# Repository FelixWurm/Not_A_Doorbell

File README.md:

# Not_A_Doorbell
This is a project aimed to build a custom "HotKey" board or mini Keyboard, using the raspberry pi pico (rp2040), an old recyceld controller (can by replaced with a standart alps encoder) and a qmc firmware. The used switches are cherry MX and compatiblt options.  It also uses RGB leds for some sweet lighing effects

The Name of the Project was selected because an early render of the device looked somewhat like a Doorbell, mainly because i only renderd the Encoder but not the buttons. 

# The Goal of the Project

I had purched a old "Video schnittpult" second hand (Televela T701), to use the housing and some of the parts for a different Project. However, the very nice encoder (also nown as jog/shutter wheel) was not realy needte. I howeve always whanted something to controll playing music with, so the idear was born to build my owen mini Keyboard.

#some tips:
in oder tu use the full potential of the endoder when usung linux set I recomend chnaging the amount the Volume chnages pear rotation to one ore two. To du this (if you are on ubuntu ):
- ``` gsettings get org.gnome.settings-daemon.plugins.media-keys volume-step ```
 - to get the currently set value
- ``` gsettings set org.gnome.settings-daemon.plugins.media-keys volume-step 1```
 - to set it to one

# PCB and Scematic

The pcb is designt in KiCad and manufacured by JLC PCB in china. THE CUURENT VERSION OF THIS PCB HAS SOME ISSUES! the issues are:
- Missing resistors for clampung voltage to 3.3 on the imput of the pico
- wrong hole placment of the lower mountung hole from the encoder
- general mounting hole misplacment

# Enclusure
- the optiginal idear for the hosing was to use wood, however in the current state that could by difficult to do with the mashines i have acsess to. 
- a STL housing that could by 3d Printet as well as a keyplate is in development
- there is a possibility for a CNC carved housung 

# ToDo 
- Fix the PCB
- Create the software
- Upload Pictures 
- Create the STL Files for the case

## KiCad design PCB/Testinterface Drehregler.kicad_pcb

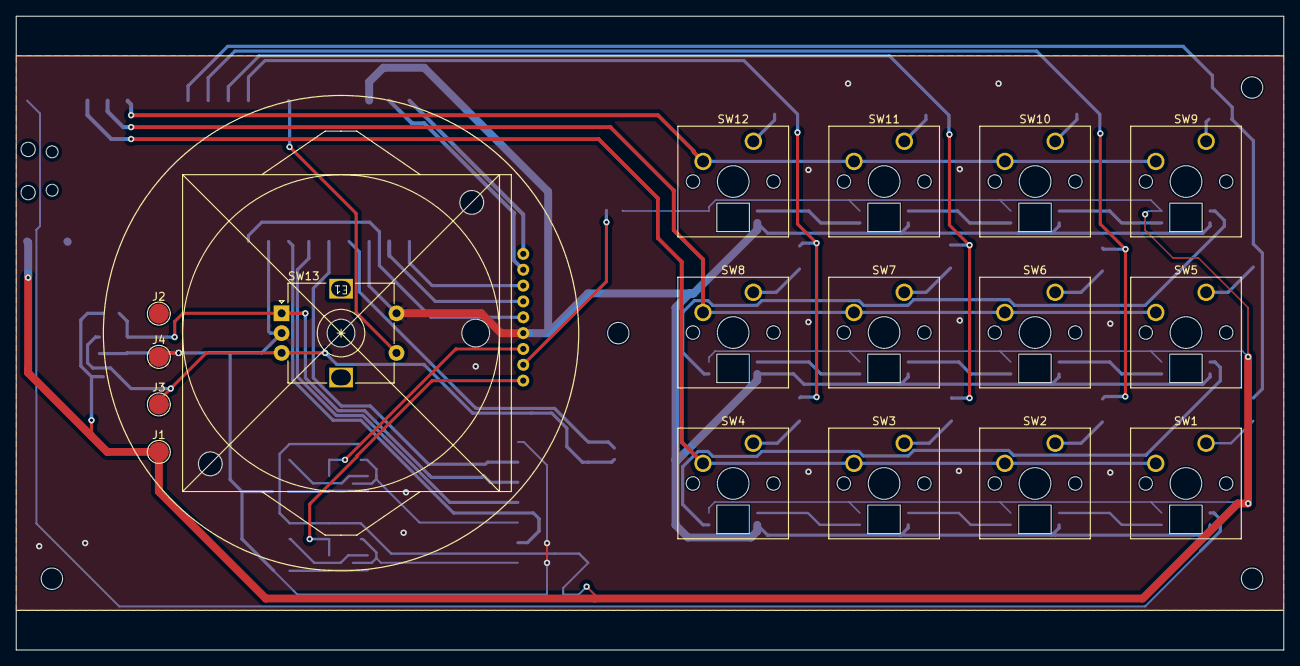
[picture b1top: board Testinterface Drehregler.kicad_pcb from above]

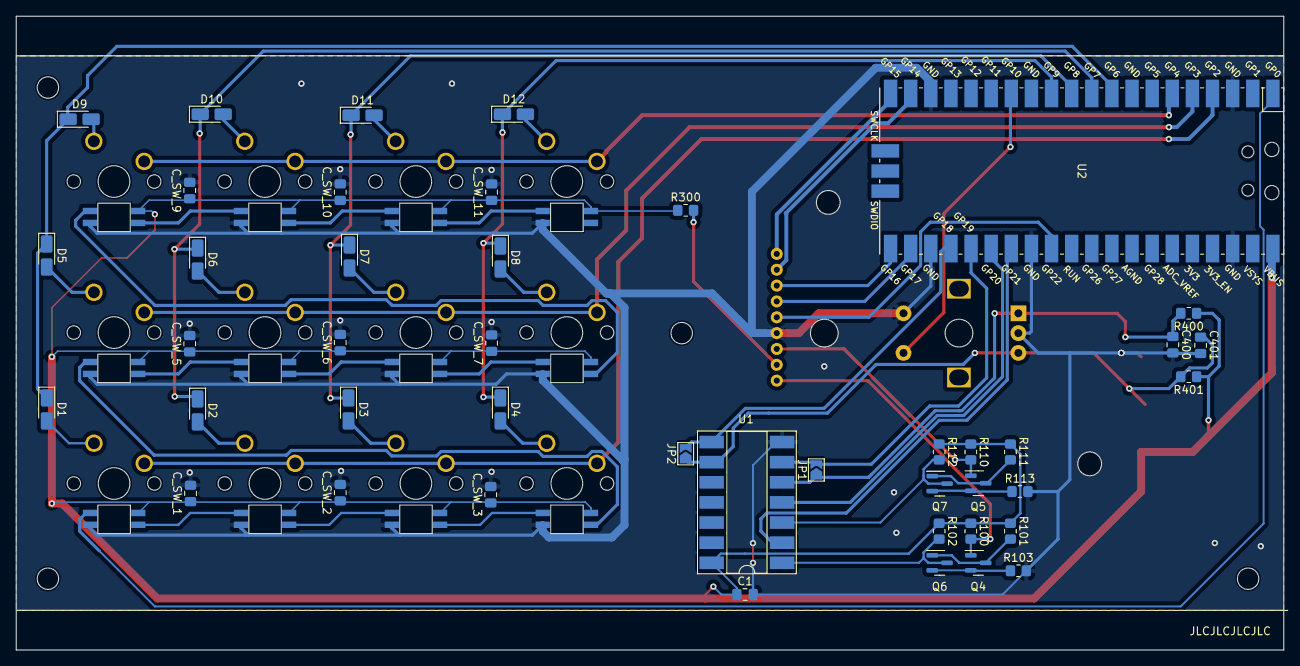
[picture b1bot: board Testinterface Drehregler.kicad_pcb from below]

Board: 2 copper layers, 160.0 x 80.0 mm, 65 parts (43 on the bottom side), 54 nets.

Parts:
C1: 100n; C_0805_2012Metric_Pad1.18x1.45mm_HandSolder
C400, C401: C; C_0805_2012Metric_Pad1.18x1.45mm_HandSolder
C_SW_1, C_SW_2, C_SW_3, C_SW_5, C_SW_6, C_SW_7, C_SW_9, C_SW_10, C_SW_11: 100nF; C_0805_2012Metric_Pad1.18x1.45mm_HandSolder
D1, D2, D3, D4, D5, D6, D7, D8, D9, D10, D11, D12: D; D_MicroMELF_Handsoldering
E1: jog_shuttel_wheal
H1, H2, H3, H4: MountingHole; MountingHole_2.7mm_M2.5
J1: ext_encoder_VCC; TestPoint_Pad_D2.5mm
J2: ext_encoder_A; TestPoint_Pad_D2.5mm
J3: ext_encoder_B; TestPoint_Pad_D2.5mm
J4: ext_encoder_GND; TestPoint_Pad_D2.5mm
JP1, JP2: SolderJumper_2_Open; SolderJumper-2_P1.3mm_Open_TrianglePad1.0x1.5mm
Q4, Q5, Q6, Q7: BC850; SOT-23
R100, R110: 47k; R_0805_2012Metric_Pad1.20x1.40mm_HandSolder
R101, R111: 180k; R_0805_2012Metric_Pad1.20x1.40mm_HandSolder
R102, R112: 10k; R_0805_2012Metric_Pad1.20x1.40mm_HandSolder
R103, R113: 1.2k; R_0805_2012Metric_Pad1.20x1.40mm_HandSolder
R300: 680; R_0805_2012Metric_Pad1.20x1.40mm_HandSolder
R400, R401: R; R_0805_2012Metric_Pad1.20x1.40mm_HandSolder
SW1, SW2, SW3, SW4, SW5, SW6, SW7, SW8, SW9, SW10, SW11, SW12: SW_Cherry_MX_1.00u_PCB_RGB
SW13: RotaryEncoder_Switch; RotaryEncoder_Alps_EC12E-Switch_Vertical_H20mm
U1: 74HC14; DIP-14_W8.89mm_SMDSocket_LongPads
U2: Pico; RPi_Pico_SMD_TH_1

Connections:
COLLUM_A: D1.1 (K), D5.1 (K), D9.1 (K), U2.9 (GPIO6)
COLLUM_B: D2.1 (K), D6.1 (K), D10.1 (K), U2.10 (GPIO7)
COLLUM_C: D3.1 (K), D7.1 (K), D11.1 (K), U2.11 (GPIO8)
COLLUM_D: D4.1 (K), D8.1 (K), D12.1 (K), U2.12 (GPIO9)
ENCODER_0_A: U1.4, U2.26 (GPIO20)
ENCODER_0_B: U1.2, U2.27 (GPIO21)
ENCODER_1_A_IN: C400.1, J2.1, JP1.1 (A), R400.2, SW13.A, U1.5
ENCODER_1_A_OUT: JP1.2 (B), U1.6, U2.25 (GPIO19)
ENCODER_1_B_IN: C401.1, J3.1, JP2.1 (A), R401.2, SW13.B, U1.9
ENCODER_1_B_OUT: JP2.2 (B), U1.8, U2.24 (GPIO18)
ENCODER_TASTER: SW13.S2, U2.14 (GPIO10)
GND: C1.2, C400.2, C401.2, C_SW_1.2, C_SW_2.2, C_SW_3.2, C_SW_5.2, C_SW_6.2, C_SW_7.2, C_SW_9.2, C_SW_10.2, C_SW_11.2, E1.6 (GND), J4.1, R103.2, R113.2, SW1.5 (LED_GND), SW2.5 (LED_GND), SW3.5 (LED_GND), SW4.5 (LED_GND), SW5.5 (LED_GND), SW6.5 (LED_GND), SW7.5 (LED_GND), SW8.5 (LED_GND), SW9.5 (LED_GND), SW10.5 (LED_GND), SW11.5 (LED_GND), SW12.5 (LED_GND), SW13.C, SW13.S1, U1.7 (GND), U2.3 (GND), U2.18 (GND), U2.23 (GND), U2.28 (GND), U2.38 (GND)
JOG_1: E1.1 (jog_1), U2.20 (GPIO15)
JOG_2: E1.2 (jog_2), U2.19 (GPIO14)
JOG_3: E1.3 (jog_3), U2.21 (GPIO16)
JOG_4: E1.4 (jog_4), U2.22 (GPIO17)
JOG_5: E1.5 (jog_5), U2.29 (GPIO22)
unnamed: D1.2 (A), SW1.1 (SW)
unnamed: D2.2 (A), SW2.1 (SW)
unnamed: D3.2 (A), SW3.1 (SW)
unnamed: D4.2 (A), SW4.1 (SW)
unnamed: D5.2 (A), SW5.1 (SW)
unnamed: D6.2 (A), SW6.1 (SW)
unnamed: D7.2 (A), SW7.1 (SW)
unnamed: D8.2 (A), SW8.1 (SW)
unnamed: D9.2 (A), SW9.1 (SW)
unnamed: D10.2 (A), SW10.1 (SW)
unnamed: D11.2 (A), SW11.1 (SW)
unnamed: D12.2 (A), SW12.1 (SW)
unnamed: E1.7 (Encoder_A), Q5.1 (B), R110.2
unnamed: E1.9 (Encoder_B), Q4.1 (B), R100.2
unnamed: E1.8 (LED_PW), R300.2
unnamed: Q4.3 (C), Q6.1 (B), R101.2
unnamed: Q4.2 (E), Q6.2 (E), R103.1
unnamed: Q5.3 (C), Q7.1 (B), R111.2
unnamed: Q5.2 (E), Q7.2 (E), R113.1
unnamed: Q6.3 (C), R102.2, U1.1
unnamed: Q7.3 (C), R112.2, U1.3
unnamed: SW1.4 (LED_OUT), SW2.6 (LED_IN)
unnamed: SW2.4 (LED_OUT), SW3.6 (LED_IN)
unnamed: SW3.4 (LED_OUT), SW4.6 (LED_IN)
unnamed: SW4.4 (LED_OUT), SW5.6 (LED_IN)
unnamed: SW5.4 (LED_OUT), SW6.6 (LED_IN)
unnamed: SW6.4 (LED_OUT), SW7.6 (LED_IN)
unnamed: SW7.4 (LED_OUT), SW8.6 (LED_IN)
unnamed: SW8.4 (LED_OUT), SW9.6 (LED_IN)
unnamed: SW9.4 (LED_OUT), SW10.6 (LED_IN)
unnamed: SW10.4 (LED_OUT), SW11.6 (LED_IN)
unnamed: SW11.4 (LED_OUT), SW12.6 (LED_IN)
RGB_DIN: SW1.6 (LED_IN), U2.1 (GPIO0)
ROW_A: SW1.2 (SW), SW2.2 (SW), SW3.2 (SW), SW4.2 (SW), U2.4 (GPIO2)
ROW_B: SW5.2 (SW), SW6.2 (SW), SW7.2 (SW), SW8.2 (SW), U2.5 (GPIO3)
ROW_C: SW9.2 (SW), SW10.2 (SW), SW11.2 (SW), SW12.2 (SW), U2.6 (GPIO4)
VCC: C1.1, C_SW_1.1, C_SW_2.1, C_SW_3.1, C_SW_5.1, C_SW_6.1, C_SW_7.1, C_SW_9.1, C_SW_10.1, C_SW_11.1, J1.1, R100.1, R101.1, R102.1, R110.1, R111.1, R112.1, R300.1, R400.1, R401.1, SW1.3 (LED_VCC), SW2.3 (LED_VCC), SW3.3 (LED_VCC), SW4.3 (LED_VCC), SW5.3 (LED_VCC), SW6.3 (LED_VCC), SW7.3 (LED_VCC), SW8.3 (LED_VCC), SW9.3 (LED_VCC), SW10.3 (LED_VCC), SW11.3 (LED_VCC), SW12.3 (LED_VCC), U1.14 (VCC), U2.40 (VBUS)

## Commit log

2023-03-20 initial pcb commit, version 0.1.1 (!not the manufactured one!) add some Voltage Dividers to not destroy the rp2040
